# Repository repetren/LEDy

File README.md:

# LEDy – ESP32-based smart floorlamp upgrade

## Description
LEDy is a hardware project designed to integrate old LED strips into the Apple HomeKit system. It uses the ESP32 microcontroller with the HomeSpan library for the Arduino framework. It supports existing hardware buttons and capacitive sensors, allowing control over brightness and on/off state for LED strips or any other 12V load.
The project consists of two parts: code and hardware. A Gerber file for the custom PCB is included. The PCB form factor is based on the physical dimensions of the original floorlamp housing but can be reused in other compact devices, as the PCB width matches the ESP32 chip.

## ESP32 and hardware
ESP32 is the core of the whole system. Thanks to the large community, Arduino support, simple networking setup, and low cost, it's the most suitable MCU for small IoT projects. The system was tested both on a dev board and on a custom PCB designed specifically for this project.
LED dimming is done via PWM through a MOSFET transistor. The control button is implemented as a capacitive sensor and needs to be tuned empirically depending on the circuit (more on this in the `main.cpp` section).

## platformio.ini
The project requires specific settings for ESP32 in the `platformio.ini` file to avoid compilation and firmware upload errors.

## HomeSpan
[HomeSpan](https://github.com/HomeSpan/HomeSpan) is a popular open-source library for ESP32 + Arduino to integrate with Apple HomeKit. For updates or custom logic, check the official documentation and examples — they’re great. This project is based on the Dimmable LED example.
** After the first flash, Wi-Fi credentials must be entered via Serial Monitor. ** For the initial connection, refer to the HomeSpan docs. Default pairing code is: **466-37-726**

## Capacitive sensor
The pin should be set manually in main.cpp, according to the ESP32 datasheet. After uploading the firmware, ESP32 starts printing raw capacitive values to the Serial Monitor.
### To define a proper threshold:
- Note the value when not touching the sensor,
- Then note the value when touching it,
- Set your threshold somewhere between those two values.

## main.cpp
The `setup()` function handles initial library setup and MCU configuration. The Serial Monitor is used for debugging, Wi-Fi setup, and status output.
The `loop()` function constantly checks the state of the capacitive button and runs `homeSpan.poll()`

## DEV_LED.h
All accessory-related logic is handled here, based on HomeSpan's structure.
`update()` — modified from HomeSpan's original to handle smooth dimming using global variables.
`touch()` — handles capacitive sensor input and syncs it with the update() function.
This setup ensures that any change made by physical input is reflected in the HomeKit app and vice versa. Global variables for power and brightness levels help maintain the last known state across different control methods.

## level_adjust()
HomeSpan controls power via 1/0 logic and brightness through PWM. But real-world LED brightness jumps harshly without smoothing.
This function introduces a 10 ms delay between the current and target brightness levels (coming from HomeKit). This creates a soft dimming effect when turning on/off, whether controlled from the app or via the capacitive button.

## Gerber files
Includes a custom PCB designed mostly with through-hole (THT) components. The ESP32 is the only part that needs SMD soldering. Power is handled via a prebuilt MP1584 module.

## Electrical characteristics
Tested with a 1-meter LED strip using a 12V / 1A power supply.

## Future improvements
- Replace button polling with proper interrupt-based input
- Add support for 3 MOSFETs to control RGB LED strips

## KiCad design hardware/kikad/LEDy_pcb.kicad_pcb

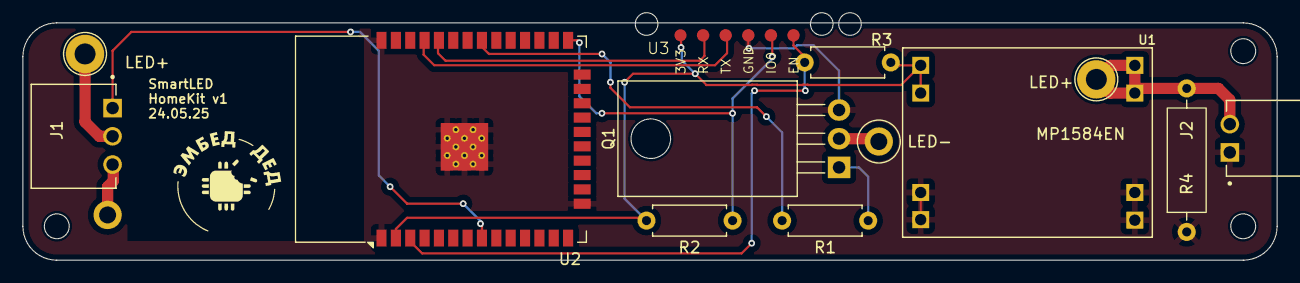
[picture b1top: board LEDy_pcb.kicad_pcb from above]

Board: 4 copper layers, 111.0 x 21.0 mm, 13 parts (0 on the bottom side), 11 nets.

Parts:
J1: 1778638; PHOENIX_1778638
J2: 1778625; PHOENIX_1778625
LED+: TestPoint_Loop_D2.50mm_Drill1.85mm
LED+#2: TestPoint_Loop_D2.50mm_Drill1.85mm
LED-: TestPoint_Loop_D2.50mm_Drill1.85mm
Q1: IRLZ44N; TO-220-3_Horizontal_TabDown
R1: 100; R_Axial_DIN0207_L6.3mm_D2.5mm_P7.62mm_Horizontal
R2, R3: 10k; R_Axial_DIN0207_L6.3mm_D2.5mm_P7.62mm_Horizontal
R4: 120 2W; R_Axial_DIN0309_L9.0mm_D3.2mm_P12.70mm_Horizontal
U1: MP1584; MP1584_AMAZON
U2: ESP32-WROOM-32
U3: Connectik v001

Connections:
+3.3V: R2.2, R3.2, U1.7 (VOUT1+), U1.8 (VOUT2+), U2.2 (VDD), U3.1 (3V3)
+12V: J1.02, J2.02, LED+.1, LED+#2.1, R4.2, U1.3 (VIN1+), U1.4 (VIN2+)
GND: J2.01, Q1.3 (S), R4.1, U1.1 (VIN1-), U1.2 (VIN2-), U1.5 (VOUT1-), U1.6 (VOUT2-), U2.1 (GND), U2.15 (GND), U2.38 (GND), U2.39 (GND), U3.4 (GND)
unnamed: J1.03, LED-.1, Q1.2 (D)
unnamed: Q1.1 (G), R1.1
unnamed: R3.1, U2.3 (EN), U3.6 (EN)
unnamed: R2.1, U2.25 (IO0), U3.5 (IO0)
unnamed: R1.2, U2.31 (IO19)
unnamed: J1.01, U2.8 (IO32)
unnamed: U2.34 (RXD0/IO3), U3.2 (RX)
unnamed: U2.35 (TXD0/IO1), U3.3 (TX)

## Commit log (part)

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2025-05-04 Home Span dimmple LED first commit
2025-05-11 Add graduate dimming
2025-05-11 Physical capacitive sensor button was added
2025-05-11 README.md
2025-06-22 LEDy - smat floorlamp upgrade v2.0
